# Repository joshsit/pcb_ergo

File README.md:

# pcb_ergo
Project files for development of custom 36 key unibody ergonomic wireless mechanical keyboard.

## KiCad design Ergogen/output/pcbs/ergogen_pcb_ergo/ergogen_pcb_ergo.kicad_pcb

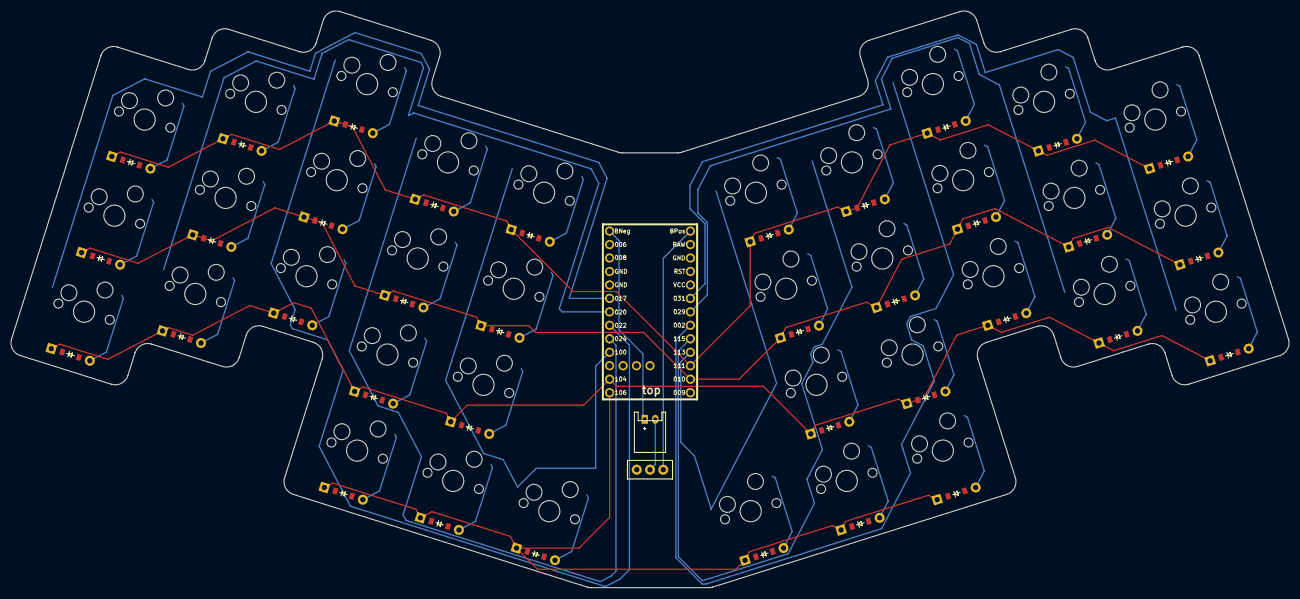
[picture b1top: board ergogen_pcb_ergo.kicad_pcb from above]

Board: 2 copper layers, 241.1 x 108.8 mm, 75 parts (0 on the bottom side), 54 nets.

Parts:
D1, D2, D3, D4, D5, D6, D7, D8, D9, D10, D11, D12, D13, D14, D15, D16, D17, D18, D19, D20, D21, D22, D23, D24, D25, D26, D27, D28, D29, D30, D31, D32, D33, D34, D35, D36: ComboDiode
JST1: JST_PH_S2B-PH-K_02x2.00mm_Angled
MCU1: nice_nano
S1, S2, S3, S4, S5, S6, S7, S8, S9, S10, S11, S12, S13, S14, S15, S16, S17, S18, S19, S20, S21, S22, S23, S24, S25, S26, S27, S28, S29, S30, S31, S32, S33, S34, S35, S36: MX
T1: 1test slide switch; 1test_slide_switch

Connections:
BPos: MCU1.26, T1.1
GND: MCU1.4, MCU1.5, MCU1.24
P002: MCU1.19, S25.1, S26.1, S27.1, S34.1
P010: D2.1, D5.1, D8.1, D11.1, D14.1, D20.1, D23.1, D26.1, D29.1, D32.1, MCU1.15
P017: MCU1.6, S1.1, S2.1, S3.1
P020: MCU1.7, S4.1, S5.1, S6.1
P022: MCU1.8, S7.1, S8.1, S9.1, S16.1
P024: MCU1.9, S10.1, S11.1, S12.1, S17.1
P029: MCU1.20, S22.1, S23.1, S24.1
P031: MCU1.21, S19.1, S20.1, S21.1
P100: MCU1.10, S13.1, S14.1, S15.1, S18.1
P104: D1.1, D4.1, D7.1, D10.1, D13.1, D19.1, D22.1, D25.1, D28.1, D31.1, MCU1.12
P106: D16.1, D17.1, D18.1, D34.1, D35.1, D36.1, MCU1.13
P111: D3.1, D6.1, D9.1, D12.1, D15.1, D21.1, D24.1, D27.1, D30.1, D33.1, MCU1.16
P113: MCU1.17, S31.1, S32.1, S33.1, S36.1
P115: MCU1.18, S28.1, S29.1, S30.1, S35.1
index_bottom: D10.2, S10.2
index_home: D11.2, S11.2
index_top: D12.2, S12.2
inner_bottom: D13.2, S13.2
inner_cluster: D16.2, S16.2
inner_home: D14.2, S14.2
inner_top: D15.2, S15.2
middle_bottom: D7.2, S7.2
middle_cluster: D17.2, S17.2
middle_home: D8.2, S8.2
middle_top: D9.2, S9.2
mirror_index_bottom: D28.2, S28.2
mirror_index_home: D29.2, S29.2
mirror_index_top: D30.2, S30.2
mirror_inner_bottom: D31.2, S31.2
mirror_inner_cluster: D34.2, S34.2
mirror_inner_home: D32.2, S32.2
mirror_inner_top: D33.2, S33.2
mirror_middle_bottom: D25.2, S25.2
mirror_middle_cluster: D35.2, S35.2
mirror_middle_home: D26.2, S26.2
mirror_middle_top: D27.2, S27.2
mirror_outer_cluster: D36.2, S36.2
mirror_pinky_bottom: D19.2, S19.2
mirror_pinky_home: D20.2, S20.2
mirror_pinky_top: D21.2, S21.2
mirror_ring_bottom: D22.2, S22.2
mirror_ring_home: D23.2, S23.2
mirror_ring_top: D24.2, S24.2
neg: JST1.2, T1.2
outer_cluster: D18.2, S18.2
pinky_bottom: D1.2, S1.2
pinky_home: D2.2, S2.2
pinky_top: D3.2, S3.2
pos: JST1.1, MCU1.1
ring_bottom: D4.2, S4.2
ring_home: D5.2, S5.2
ring_top: D6.2, S6.2

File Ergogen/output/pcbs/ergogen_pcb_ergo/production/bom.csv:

Designator,Footprint,Quantity,Value,LCSC Part #
"D1, D10, D11, D12, D13, D14, D15, D16, D17, D18, D19, D2, D20, D21, D22, D23, D24, D25, D26, D27, D28, D29, D3, D30, D31, D32, D33, D34, D35, D36, D4, D5, D6, D7, D8, D9",ComboDiode,36,,
JST1,JST_PH_S2B-PH-K_02x2.00mm_Angled,1,,
MCU1,nice_nano,1,nice_nano,
"S1, S10, S11, S12, S13, S14, S15, S16, S17, S18, S19, S2, S20, S21, S22, S23, S24, S25, S26, S27, S28, S29, S3, S30, S31, S32, S33, S34, S35, S36, S4, S5, S6, S7, S8, S9",MX,36,,
T1,1test_slide_switch,1,1test slide switch,

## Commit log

2025-07-15 initial push
2025-07-15 added ergogen config
2025-07-15 added footprint
2025-07-25 updating ergogen layout
2025-07-25 more updates to ergogen config
2025-07-25 new changes, updated ergogen footprints for slider switch and nice nano (to have thirteen pins)
2025-08-07 updates to wired and wireless builds
2025-08-08 experimental jscad ergogen outputs for cases
